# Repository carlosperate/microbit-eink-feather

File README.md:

# micro:bit eInk Feather Adaptor

This is a simple FeatherWing to micro:bit adaptor board designed specifically
for the Adafruit 2.9" Grayscale eInk / ePaper Display FeatherWing:
https://www.adafruit.com/product/4777

## Repository Contents

- **datasheets**: Datasheets for the components used in this adaptor board
- **docs**: Documentation related to this adaptor board
- **firmware**: Arduino Skectch to test the eInk FeatherWing with a micro:bit
- **hardware**: The KiCad project files
- **output**: Project output files, like the BOM, schematic PDFs, etc.
    - **interactive_bom**: BOM output from the
      [Interactive HTML BOM](https://github.com/openscopeproject/InteractiveHtmlBom)
      KiCad plugin.
    - **pdf**: Schematic PDFs.
    - **production**: Gerber and drill files.

## Documentation

- Pinout connections for the adaptor board: [docs/pins.md](docs/pins.md)
- [eInk FeatherWing product page](https://www.adafruit.com/product/4777)
- [Adafruit documentation for the eInk FeatherWing](https://learn.adafruit.com/adafruit-eink-display-breakouts/grayscale-29-overview)
- [Documentation for the family of Adafruit 2.9" eInk Display Breakouts and FeatherWings](https://learn.adafruit.com/adafruit-2-9-eink-display-breakouts-and-featherwings/)
- Project Changelog: [CHANGELOG.md](CHANGELOG.md)

## License & Attributions

The Arduino test sketch is based on the
[Adafruit EDP ThinkInk_gray4 example][6], with [MIT License][7].

The micro:bit edge connector is [MIT Licensed][8] and comes from:
https://github.com/anthonykirby/kicad_microbit_connector

This project has been based on this FeatherWing template:
https://github.com/ppelleti/FeatherWing-template-KiCad

The FeatherWing template and the rest of the repository (except where stated
otherwise) is licensed under [the same terms as the KiCad libraries][9],
which is the [CC-BY-SA 4.0][10] license, with an exception that says that
electronic designs based on this repository are not bound by the attribution
and share-alike conditions.

[6]: https://github.com/adafruit/Adafruit_EPD/blob/4.4.3/examples/ThinkInk_gray4/ThinkInk_gray4.ino
[7]: firmware/eink_feather_test/LICENSE
[8]: hardware/microbit_connector/LICENSE
[9]: https://forum.kicad.info/t/kicad-library-licensing/7856
[10]: https://creativecommons.org/licenses/by-sa/4.0/legalcode

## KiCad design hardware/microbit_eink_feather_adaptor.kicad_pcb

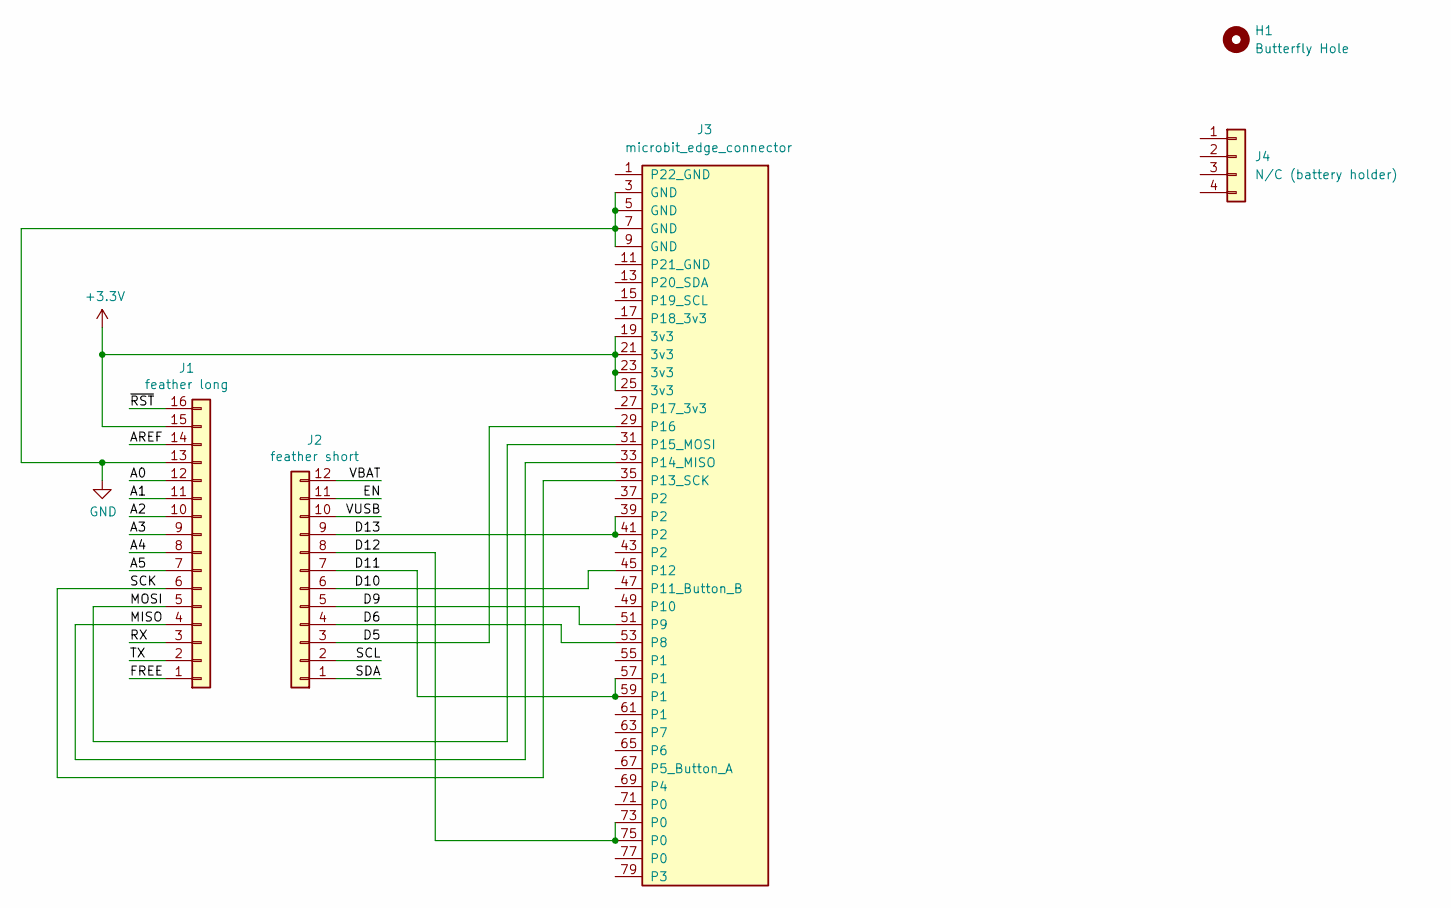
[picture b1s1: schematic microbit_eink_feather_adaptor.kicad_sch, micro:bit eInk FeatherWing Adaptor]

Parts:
H1: Butterfly Hole; butterfly_hole
J1: feather long; PinHeader_1x16_P2.54mm_Vertical
J2: feather short; PinHeader_1x12_P2.54mm_Vertical
J3: microbit_edge_connector; 4UCON_10156_2x40_P1.27mm_Socket_Horizontal
J4: N/C (battery holder); PinHeader_1x04_P2.54mm_Vertical

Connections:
+3V3: J1.15, J3.19 (3v3), J3.21 (3v3), J3.23 (3v3), J3.25 (3v3)
/A0: J1.12
/A1: J1.11
/A2: J1.10
/A3: J1.9
/A4: J1.8
/A5: J1.7
/AREF: J1.14
/D5: J2.3, J3.29 (P16)
/D6: J2.4, J3.53 (P8)
/D9: J2.5, J3.51 (P9)
/D10: J2.6, J3.45 (P12)
/D11: J2.7, J3.57 (P1), J3.59 (P1)
/D12: J2.8, J3.73 (P0), J3.75 (P0)
/D13: J2.9, J3.39 (P2), J3.41 (P2)
/EN: J2.11
/FREE: J1.1
/MISO: J1.4, J3.33 (P14_MISO)
/MOSI: J1.5, J3.31 (P15_MOSI)
/RX: J1.3
/SCK: J1.6, J3.35 (P13_SCK)
/SCL: J2.2
/SDA: J2.1
/TX: J1.2
/VBAT: J2.12
/VUSB: J2.10
/~RST: J1.16
GND: J1.13, J3.3 (GND), J3.5 (GND), J3.7 (GND), J3.9 (GND)

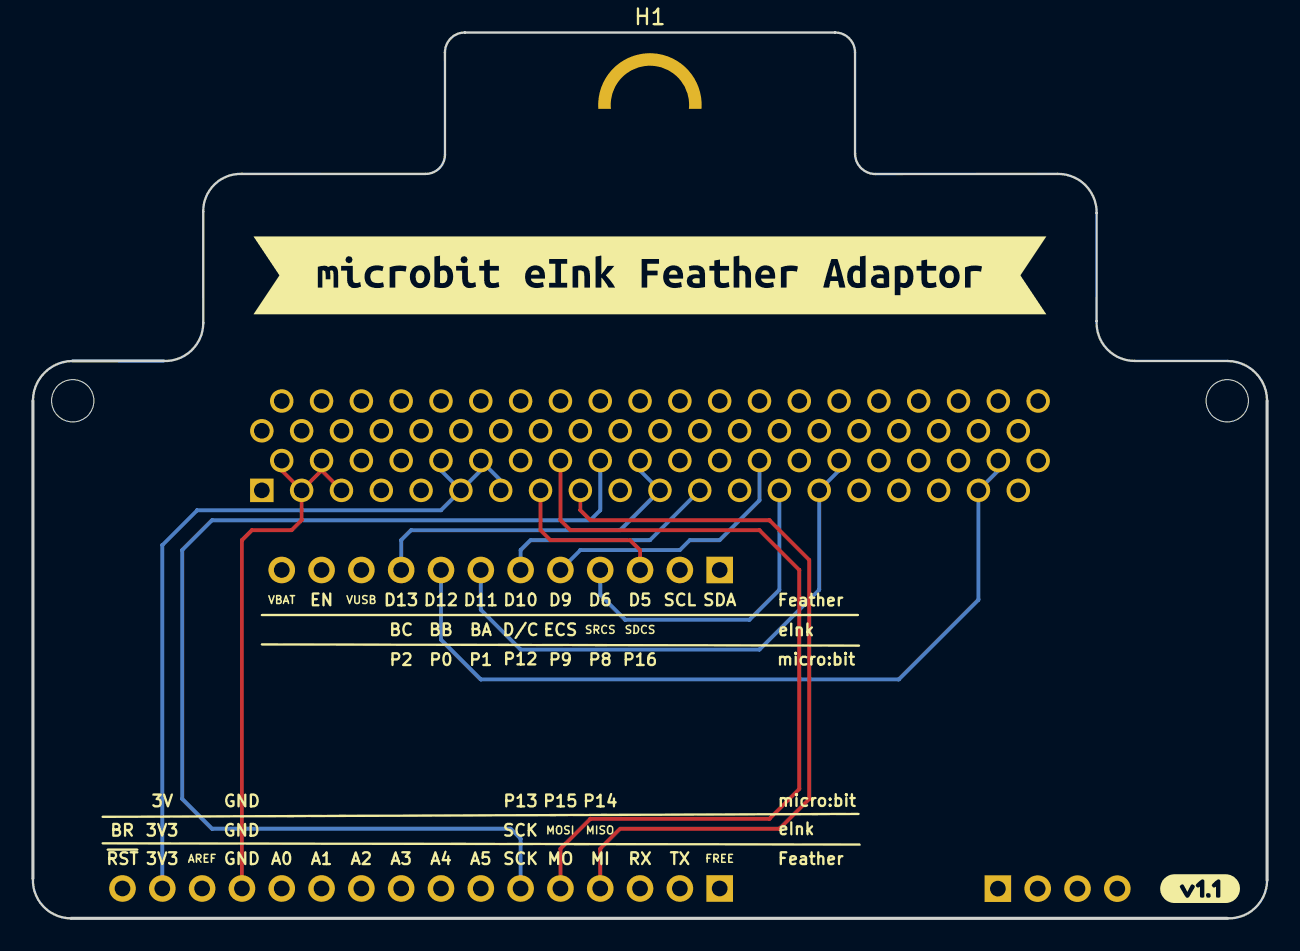
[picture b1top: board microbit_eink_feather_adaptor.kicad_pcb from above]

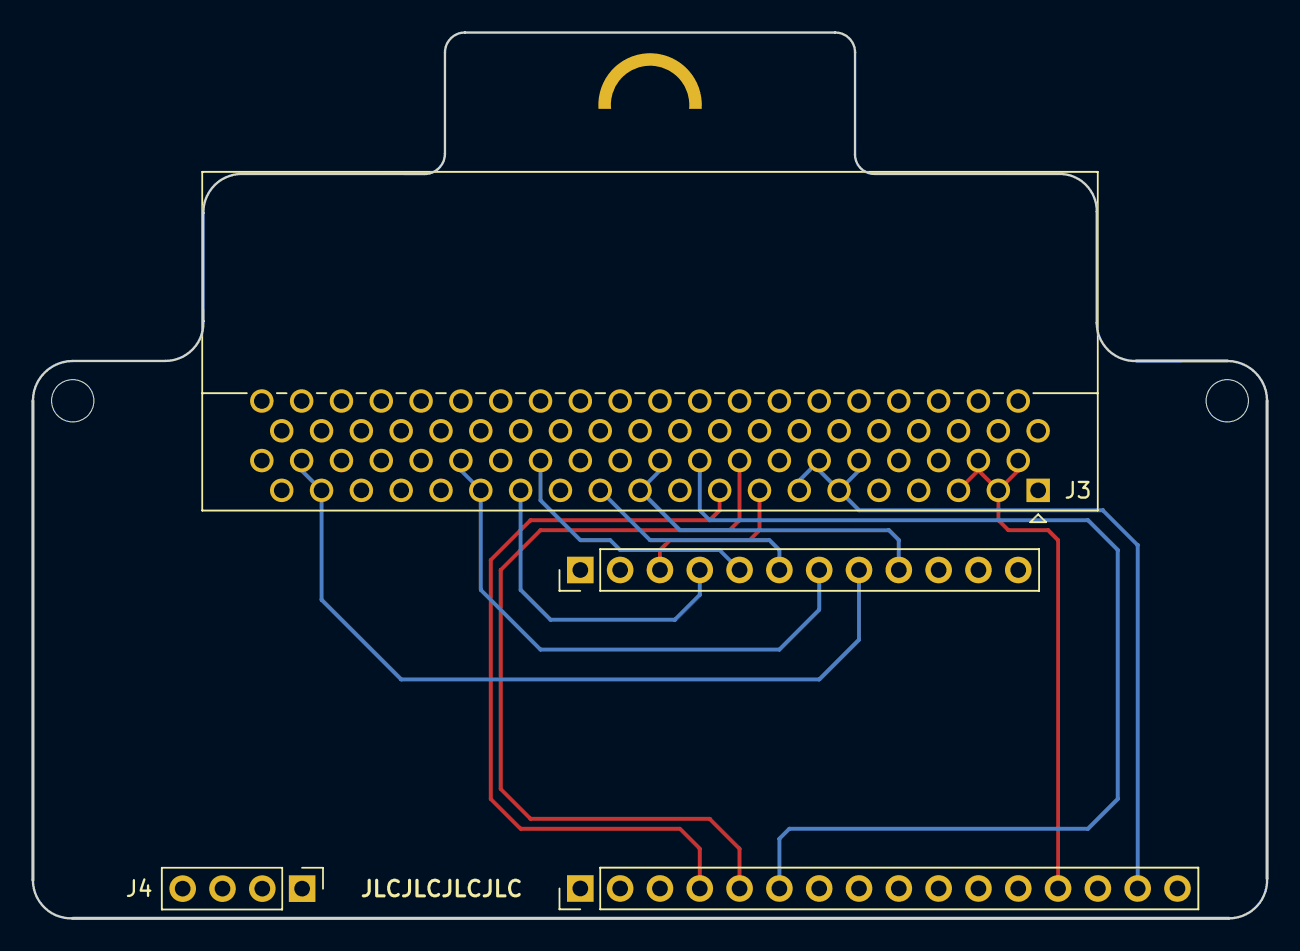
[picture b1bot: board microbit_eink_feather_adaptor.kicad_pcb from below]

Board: 2 copper layers, 78.7 x 56.5 mm, 7 parts (4 on the bottom side), 12 nets.

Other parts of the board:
kibuzzard-62B8B88C: G***; kibuzzard-62B8B88C
kibuzzard-62B89D05: G***; kibuzzard-62B89D05

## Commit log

2022-06-05 Add origin "FeatherWing_KC5" project before editing it.
2022-06-06 Update project from KiCARd 5 to 6.
2022-06-06 Add unmodified micro:bit conector library.
2022-06-06 Add micro:bit edge connector to project.
2022-06-06 Increase board size, place edge connector, and route 3V, GND, and SPI pins.
2022-06-06 Add docs about pinouts.
2022-06-06 Add datasheet for the micro:bit edge connector.
2022-06-07 Complete pinout documentation and update README.
2022-06-07 Route all pins and complete initial version of board.
2022-06-07 Add production files for manufacturing of initial V1.0
2022-06-07 Add CHANGELOG an update README.
2022-06-12 fw: Add a test Arduino Sketch.
2022-06-12 ci: Add GitHub Action to compile Arduino test Sketch.
2022-06-12 docs: Minor updates to pin info and README.
2022-06-12 ci: Add Arduino Link job to Arduino workflow.
2022-06-12 fw: Rename Sketch to denote is a test programme, add LICENSE.
2022-06-26 output: Add output directory for schematic PDFs
2022-06-27 pcb: Expand PCB to include butterfly hang hole.
2022-06-27 pcb: Replace butterfly hole with custom footprint.
2022-06-27 schematic & pcb: Add (optional) header to physically hold battery.
2022-06-27 output: Add BOM & mode production folder inside output.
2022-06-27 production: Update gerber and drill files for v1.1 build.
2022-06-28 schematic: Update PDF output to v1.1 version.
2022-06-28 docs: Add image of v1.1 to README and README to BOM folder.
2022-07-01 fw: Add code to show hearts in the micro:bit display.
2022-07-08 fw: Add micro:bit Arduino library as dependency.
2023-07-06 fw: Add another example to display bmp from sd card.
